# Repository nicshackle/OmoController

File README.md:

# OmoController
###### A wearable game controller that tracks scalar hand motion

The omo controller was designed to be embedded in the cuff of a boxing glove. When a punch is thrown, the unit transmits that event to a receiver, which was connected to a bespoke computer game. 

The unit has headers for an Xbee radio, which it would use to transmit data.

The controller measures 4x3x1.5cm, including 500mAh LiPo battery. The unit has charging circuitry on-board, which allows for charging from USB power.

The below controller travelled around South Africa as part of a promotional installation. 

## Schematic

## Parts

|Part|Name|
|:---|:---|
|Microcontroller|Atmel 328P, 3.3V, 8MHz|
|Accelerometer|NXP MMA8652FC|
|Charge controller|MAX1555|
|LDO Voltage Regulator|TI TPS73733†|

†This part has a dropout of 130mV, i.e. it will drop out at 3.43V. This voltage is very near the total depletion point of LiPo batteries, which means the device is able to make use of most of the battery's charge. 

## Programming

 - Use 3.3v ICSP programmer
 - If using a fresh chip, burn the Arduino 3.3V 8MHz bootloader to set fuse bits

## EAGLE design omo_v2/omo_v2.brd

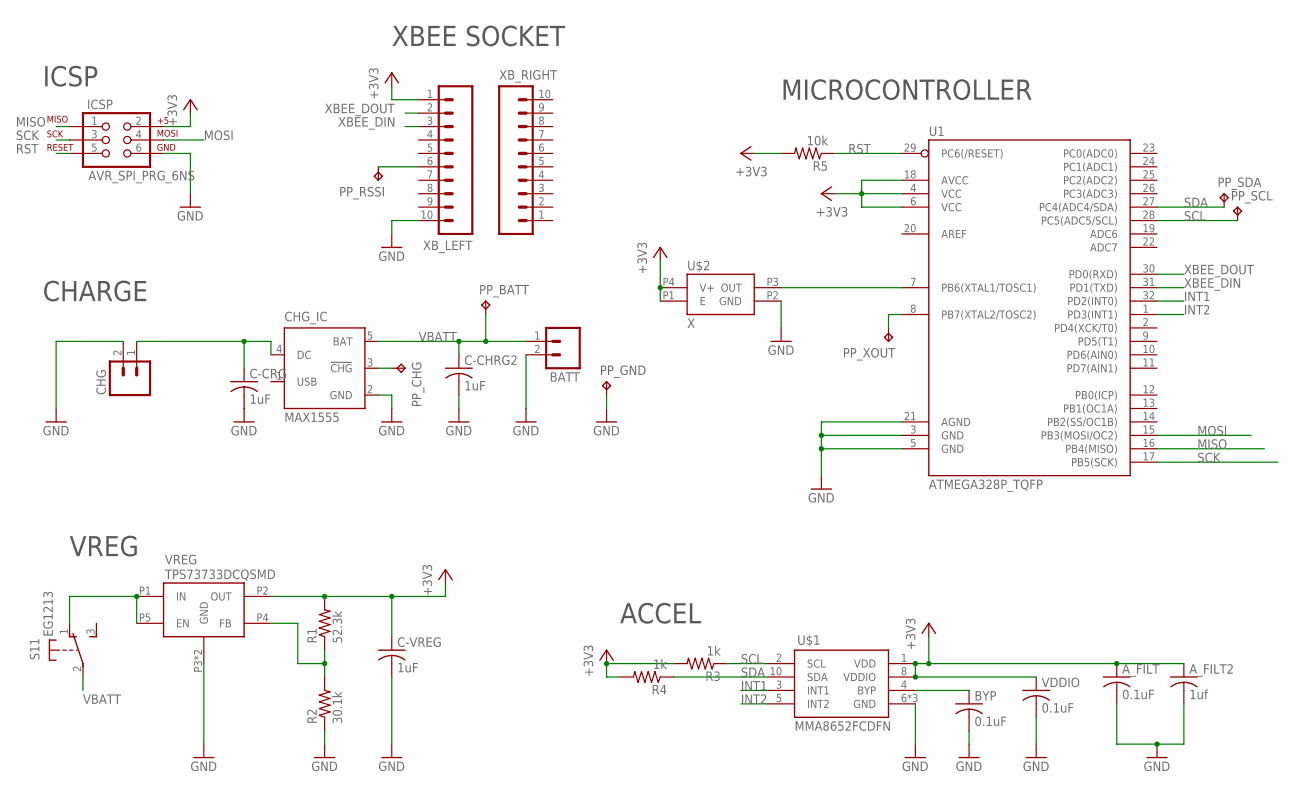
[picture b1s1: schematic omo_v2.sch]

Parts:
A_FILT: 0.1uF; C0805
A_FILT2: 1uf; C0805
BATT: M02-JST-2-PTH-NO_SILK; JST-2-PTH-NS
BYP: 0.1uF; C0805
C-CHRG2: 1uF; C0805
C-CRG: 1uF; C0805
C-VREG: 1uF; C0805
CHG: M02-JST-2-PTH-NO_SILK; JST-2-PTH-NS
CHG_IC: MAX1555; SOT23-5L
ICSP: AVR_SPI_PRG_6NS; 2X3-NS
PP_BATT: TPB1,27; B1,27
PP_CHG: TPB1,27; B1,27
PP_GND: TPB1,27; B1,27
PP_RSSI: TPB1,27; B1,27
PP_SCL: TPB1,27; B1,27
PP_SDA: TPB1,27; B1,27
PP_XOUT: TPB1,27; B1,27
R1: 52.3k; R0805
R2: 30.1k; R0805
R3, R4: 1k; R0805
R5: 10k; R0805
S1: EG1213
U1: ATMEGA328P_TQFP; TQFP32-08
U$1: MMA8652FCDFN; MMA8652FC
U$2: X; QX3-OSC-3.2X2.5
VDDIO: 0.1uF; C0805
VREG: TPS73733DCQSMD; SOT-223-6
XB_LEFT: M102MM; 1X10-2MM
XB_RIGHT: M102MM; 1X10-2MM

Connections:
+3V3: A_FILT.1, A_FILT2.1, C-VREG.1, ICSP.2, R1.2, R3.2, R4.2, R5.2, U1.4 (VCC), U1.6 (VCC), U1.18 (AVCC), U$1.1 (VDD), U$1.8 (VDDIO), U$2.P1 (E), U$2.P4 (V+), VDDIO.1, VREG.P2 (OUT), XB_LEFT.1
GND: A_FILT.2, A_FILT2.2, BATT.2, BYP.2, C-CHRG2.2, C-CRG.2, C-VREG.2, CHG.2, CHG_IC.2 (GND), ICSP.6, PP_GND.TP, R2.1, U1.3 (GND), U1.5 (GND), U1.21 (AGND), U$1.6 (GND), U$1.7 (GND), U$1.9 (GND), U$2.P2 (GND), VDDIO.2, VREG.P3 (GND), VREG.P6 (GND), XB_LEFT.10
INT1: U1.32 (PD2(INT0)), U$1.3 (INT1)
INT2: U1.1 (PD3(INT1)), U$1.5 (INT2)
MISO: ICSP.1, U1.16 (PB4(MISO))
MOSI: ICSP.4, U1.15 (PB3(MOSI/OC2))
unnamed: CHG_IC.3 (!CHG), PP_CHG.TP
unnamed: PP_RSSI.TP, XB_LEFT.6
unnamed: R1.1, R2.2, VREG.P4 (FB)
unnamed: S1.1 (O), VREG.P1 (IN), VREG.P5 (EN)
unnamed: PP_XOUT.TP, U1.8 (PB7(XTAL2/TOSC2))
unnamed: U1.7 (PB6(XTAL1/TOSC1)), U$2.P3 (OUT)
unnamed: BYP.1, U$1.4 (BYP)
RST: ICSP.5, R5.1, U1.29 (PC6(/RESET))
SCK: ICSP.3, U1.17 (PB5(SCK))
SCL: PP_SCL.TP, R3.1, U1.28 (PC5(ADC5/SCL)), U$1.2 (SCL)
SDA: PP_SDA.TP, R4.1, U1.27 (PC4(ADC4/SDA)), U$1.10 (SDA)
VBATT: BATT.1, C-CHRG2.1, CHG_IC.5 (BAT), PP_BATT.TP, S1.2
VUSB: C-CRG.1, CHG.1, CHG_IC.4 (DC)
XBEE_DIN: U1.31 (PD1(TXD)), XB_LEFT.3
XBEE_DOUT: U1.30 (PD0(RXD)), XB_LEFT.2

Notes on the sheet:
VREG
CHARGE
ACCEL
ICSP
XBEE SOCKET
MICROCONTROLLER

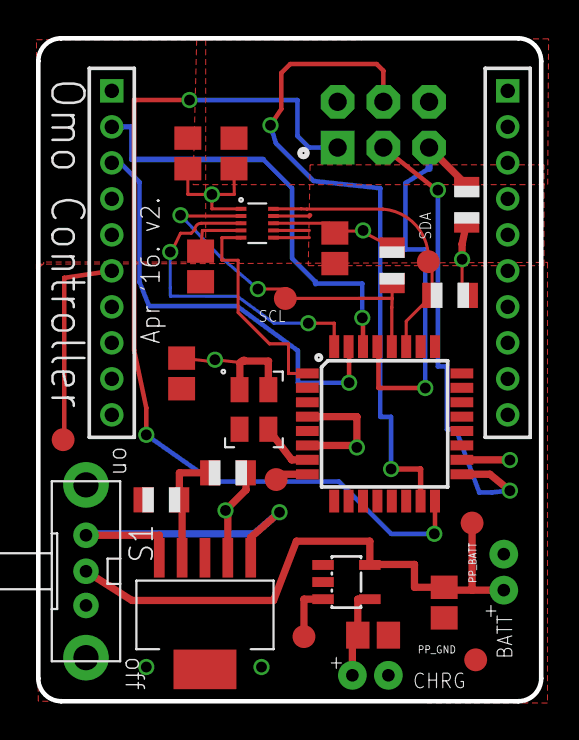
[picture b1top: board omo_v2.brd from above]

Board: 2 copper layers, 27.9 x 36.8 mm, 30 parts (0 on the bottom side), 21 nets.

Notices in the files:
parts and their libraries:
SparkFun-Connectors: Licensing: Creative Commons ShareAlike 4.0 International - https://creativecommons.org/licenses/by-sa/4.0
